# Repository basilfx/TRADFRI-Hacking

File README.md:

# Hacking IKEA TRÅDFRI

  * [Introduction](#introduction)
  * [TRÅDFRI modules](#trådfri-modules)
  * [Product teardowns](#product-teardowns)
  * [Firmware hacking](#firmware-hacking)
  * [Other hacks](#other-hacks)
    * [EZSP Zigbee coordinator](#ezsp-zigbee-coordinator)
    * [Zigbee router](#zigbee-router)
    * [FLOALT brightness hack](#floalt-brightness-hack)
    * [Shortcut button "no double press" hack](#shortcut-button-no-double-press-hack)
    * [DOOM](#doom)
  * [Sources](#sources)
  * [License](#license)
  * [Safety](#safety)
  * [Disclaimer](#disclaimer)

## Introduction
The [IKEA TRÅDFRI](http://www.ikea.com/us/en/catalog/categories/departments/lighting/36812/)
family of products provide you with several home automation solutions that
interconnect using [Zigbee Light Link](http://www.zigbee.org/zigbee-for-developers/applicationstandards/zigbee-light-link/).
While the line-up initially only included lighting products, it includes power
switches and wireless window blinds as well.

Many of the TRÅDFRI are quite simple. For instance, if we take a simple light
bulb, it contains:

* Power supply
* LED driver
* IKEA TRÅDFRI module

The IKEA TRÅDFRI module is used in many of their products, and is actually
a small piece of circuit board with a few GPIO pins exposed. These pins are
then used to control the LED driver.

The goal of this project is to provide information about the IKEA TRÅDFRI
modules and products, so you can start hacking them. For example:

* Take apart a light bulb, and use the module board, to control your own
  lighting solutions.
* Create custom boards for wall-mounted switches based on their dimmer buttons.
* Patch the firmware to dimming capabilies.
* Repurposing the modules by writing your own firmware.

To find relevant products, I have compiled a list of IKEA TRÅDFRI products in
[PRODUCTS.md](PRODUCTS.md). A teardown of has also been provided for some
products.

## TRÅDFRI modules
So far, a few variations of the TRÅDFRI modules have been identified. They are
all using microcontrollers manufactured by Silicon Labs. The modules that have
been identified are:

* ICC-1
* ICC-A-1
* MGM210L

Some other products, such as the line-up of remote controls, have a dedicated
circuit board that integrate a microcontroller directly (i.e. no separate
module board).

More details and pictures on these modules can be found in
[MODULES.md](MODULES.md).

## Product teardowns
Be sure to check out the [PRODUCTS.md](PRODUCTS.md) on more details on products
that have been reversed-engineered. There are product teardown photos,
schematics, firmware dumps, firmware analysis and more.

If you have any products not in the list, please contribute! If you have any
teardown photos, firmware files or other information, I'd like to add it to the
list.

## Firmware hacking
The TRÅDFRI products use an ARM Cortex M-series microcontroller. There are
plenty of tools for these types of microcontrollers to get started on reversing
firmware files and write your own firmwares.

* Find dumps of firmware files in the OTA [folder](contrib/firmwares/ikea-ota).
* Checkout the [RIOT-OS](contrib/firmwares/riot-os) folder for more information
  on custom firmware development. You can use this as a starting point.
* Reference information on dumping firmware images [here](docs/firmware_dumping/README.md).
* Learn how to inspect the firmware for reverse-enginering in [this](docs/firmware_reversing)
  folder.
* Build a [development board](contrib/pcbs/devboard) for easy access to a
  TRÅDFRI module's pins.

## Other hacks
Some people have came up with alternative uses for the TRÅDFRI modules. Here
are a few:

### EZSP Zigbee coordinator
It is possible to load the Silicon Labs EmberZNet Zigbee coordinator firmware
on an ICC-1 or ICC-A-1. This allows you to use the module to set-up your own
Zigbee network.

MattWestb has provided a guide and firmware [here](https://github.com/MattWestb/IKEA-TRADFRI-ICC-A-1-Module).

### Zigbee router
Several users have [modified](https://community.home-assistant.io/t/sonoff-zbbridge-sonoff-zigbee-bridge-from-itead/187346/88)
the TRÅDFRI routers to improve the performance, by adding an external antenna.

This applies to the ICC-A-1 modules only, but it should be very interesting
if a the TRÅDFRI routers will use the newer MGM210L modules, because they offer
a solder pad for an external antenna.

### FLOALT brightness hack
[zw](https://github.com/zw) has patched the firmware of his FLOALT LED panel to
have an improved range of brightness levels. A guide to perform the firmware
patch has been contributed [here](https://github.com/zw/TRADFRI-Hacking/tree/master/hacks/L1527).

### Shortcut button "no double press" hack
Simon has [patched](https://github.com/nomis/ikea-tradfri-e1812) the firmware
of the E1812 shortcut button to disable the double press feature, getting rid
of the 400ms delay on single presses.

### DOOM
A version of DOOM was port to the IKEA TRÅDFRI MGM210L modules, including a
custom contrller. The project is documented [here](https://next-hack.com/index.php/2021/06/12/lets-port-doom-to-an-ikea-tradfri-lamp/)
and the source code can be found [here](https://github.com/next-hack/MG21DOOM).

## Sources
I have gathered some information from the following sources:

* [IKEA TRÅDFRI hacking](https://tradfri.blogspot.nl)
* [TRÅDFRI: ESP8266-Lampen-Gateway](https://www.heise.de/make/artikel/Ikea-Tradfri-Anleitung-fuer-ein-ESP8266-Lampen-Gateway-3598411.html)
* [TRÅDFRI Zigbee Light Link module](https://diystuff.nl/tradfri/tradfri-zigbee-light-link-module)
* [TRÅDFRI Wall switch](https://wiki.permejdal.dk/TR%C3%85DFRI_wall_switch)

## License
See the [LICENSE.md](LICENSE.md) file (CC-BY-4.0).

## Safety
Some TRÅDFRI products are mains powered. If you don't know what that means, then
stop right now. Please read [this](docs/working_safely) for more information on
working safely on mains-connected devices.

## Disclaimer
This page and its content is not affiliated with IKEA of Sweden AB.

The purpose of this project is to learn and improve using reverse engineering
techniques. Use this information on your own risk. You will void your warranty.

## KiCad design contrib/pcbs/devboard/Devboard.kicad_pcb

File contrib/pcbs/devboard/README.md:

# Devboard
Development board to house an ICC-A or ICC-A-1 TRÅDFRI module.

## Known issues
* This board has a non-optimal design for wireless usage. However, the main
  goal of this board is to provide easier pin access.

## Pictures

## Board

## Schema
You can find the schema [here](Devboard.pdf).

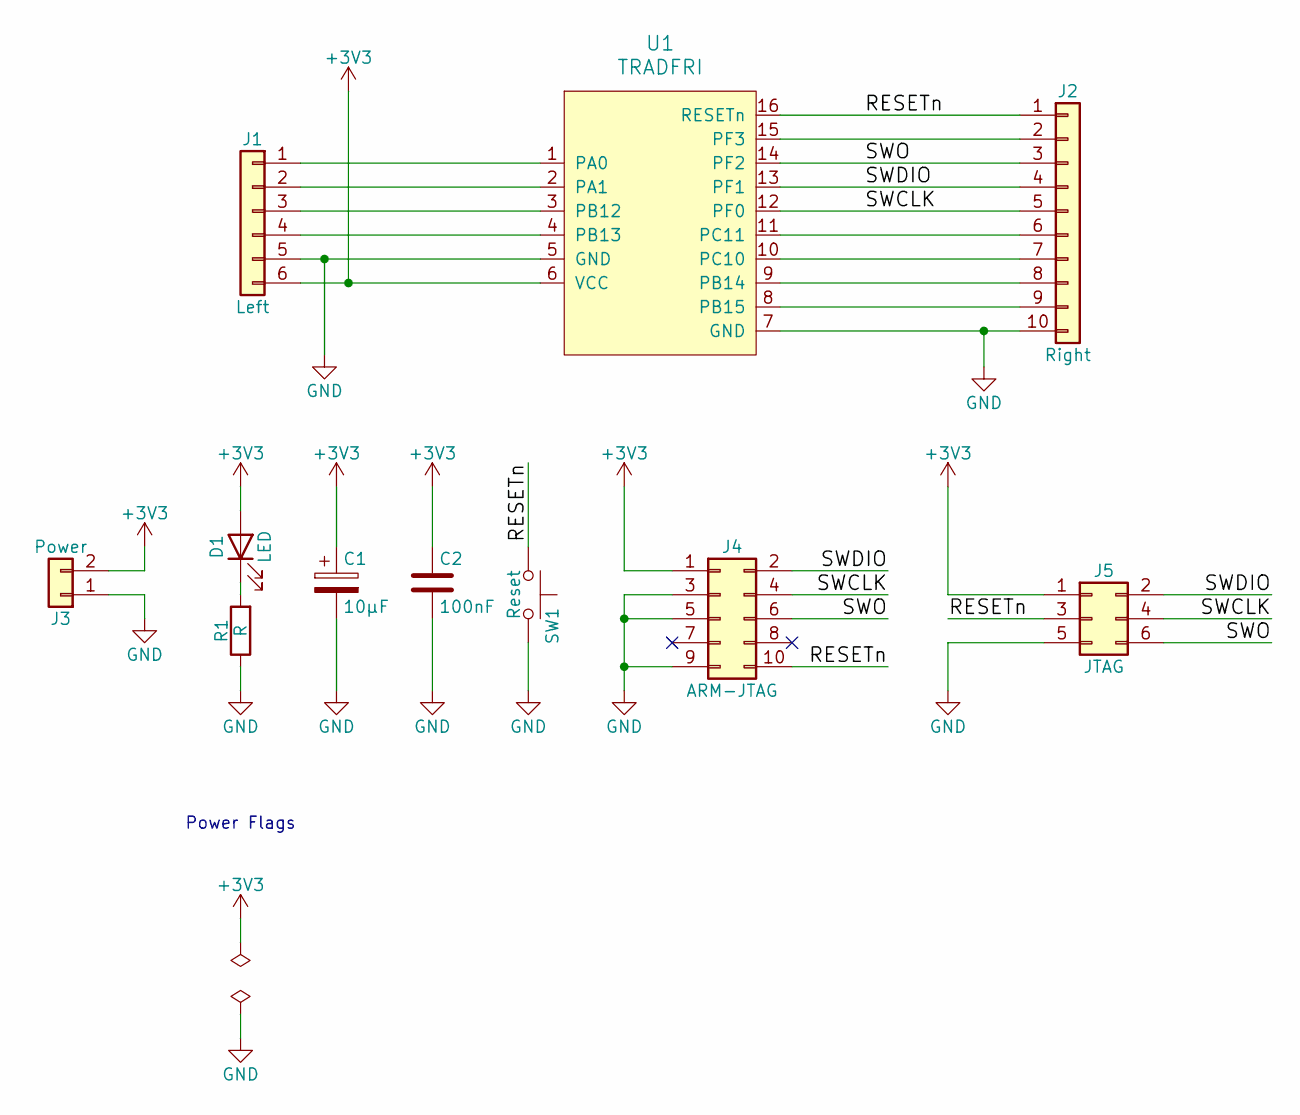
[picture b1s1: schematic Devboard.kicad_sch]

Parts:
C1: 10µF; CP_Elec_3x5.3
C2: 100nF; C_0805_2012Metric_Pad1.18x1.45mm_HandSolder
D1: LED; LED_0805_2012Metric_Pad1.15x1.40mm_HandSolder
J1: Left; PinHeader_1x06_P2.54mm_Vertical
J2: Right; PinHeader_1x10_P2.54mm_Vertical
J3: Power; PinHeader_1x02_P2.54mm_Vertical
J4: ARM-JTAG; PinHeader_2x05_P1.27mm_Vertical
J5: JTAG; PinHeader_2x03_P2.54mm_Vertical
R1: R; R_0805_2012Metric_Pad1.20x1.40mm_HandSolder
SW1: Reset; SW_PUSH_6mm
U1: TRADFRI; TRADFRI_PCB2.0

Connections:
+3V3: C1.1, C2.1, D1.2 (A), J1.6, J3.2, J4.1, J5.1, U1.6 (VCC)
/RESETn: J2.1, J4.10, J5.3, SW1.1, U1.16 (RESETn)
/SWCLK: J2.5, J4.4, J5.4, U1.12 (PF0)
/SWDIO: J2.4, J4.2, J5.2, U1.13 (PF1)
/SWO: J2.3, J4.6, J5.6, U1.14 (PF2)
GND: C1.2, C2.2, J1.5, J2.10, J3.1, J4.3, J4.5, J4.9, J5.5, R1.1, SW1.2, U1.5 (GND), U1.7 (GND)
unnamed: D1.1 (K), R1.2
unnamed: J1.1, U1.1 (PA0)
unnamed: J1.2, U1.2 (PA1)
unnamed: J1.3, U1.3 (PB12)
unnamed: J1.4, U1.4 (PB13)
unnamed: J2.2, U1.15 (PF3)
unnamed: J2.6, U1.11 (PC11)
unnamed: J2.7, U1.10 (PC10)
unnamed: J2.8, U1.9 (PB14)
unnamed: J2.9, U1.8 (PB15)

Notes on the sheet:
Power Flags

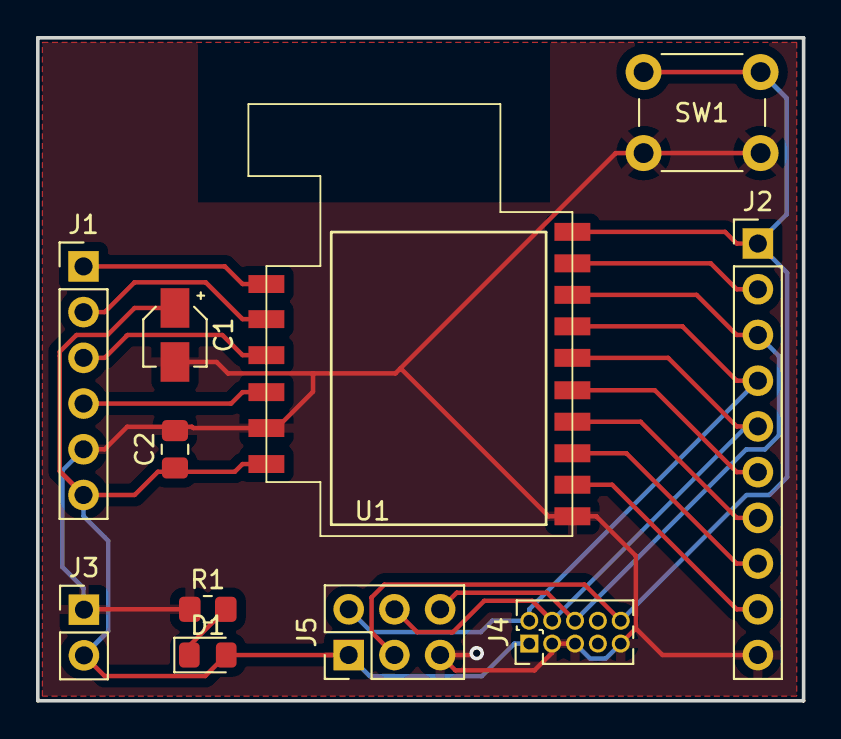
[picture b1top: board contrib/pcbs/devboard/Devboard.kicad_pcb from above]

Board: 2 copper layers, 42.5 x 36.8 mm, 11 parts (0 on the bottom side), 16 nets.

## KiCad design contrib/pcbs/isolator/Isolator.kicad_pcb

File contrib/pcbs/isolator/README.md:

# Isolator
Tiny board to isolate UART RX/TX from target board.

## Pictures

## Board

## Schema
You can find the schema [here](Isolator.pdf).

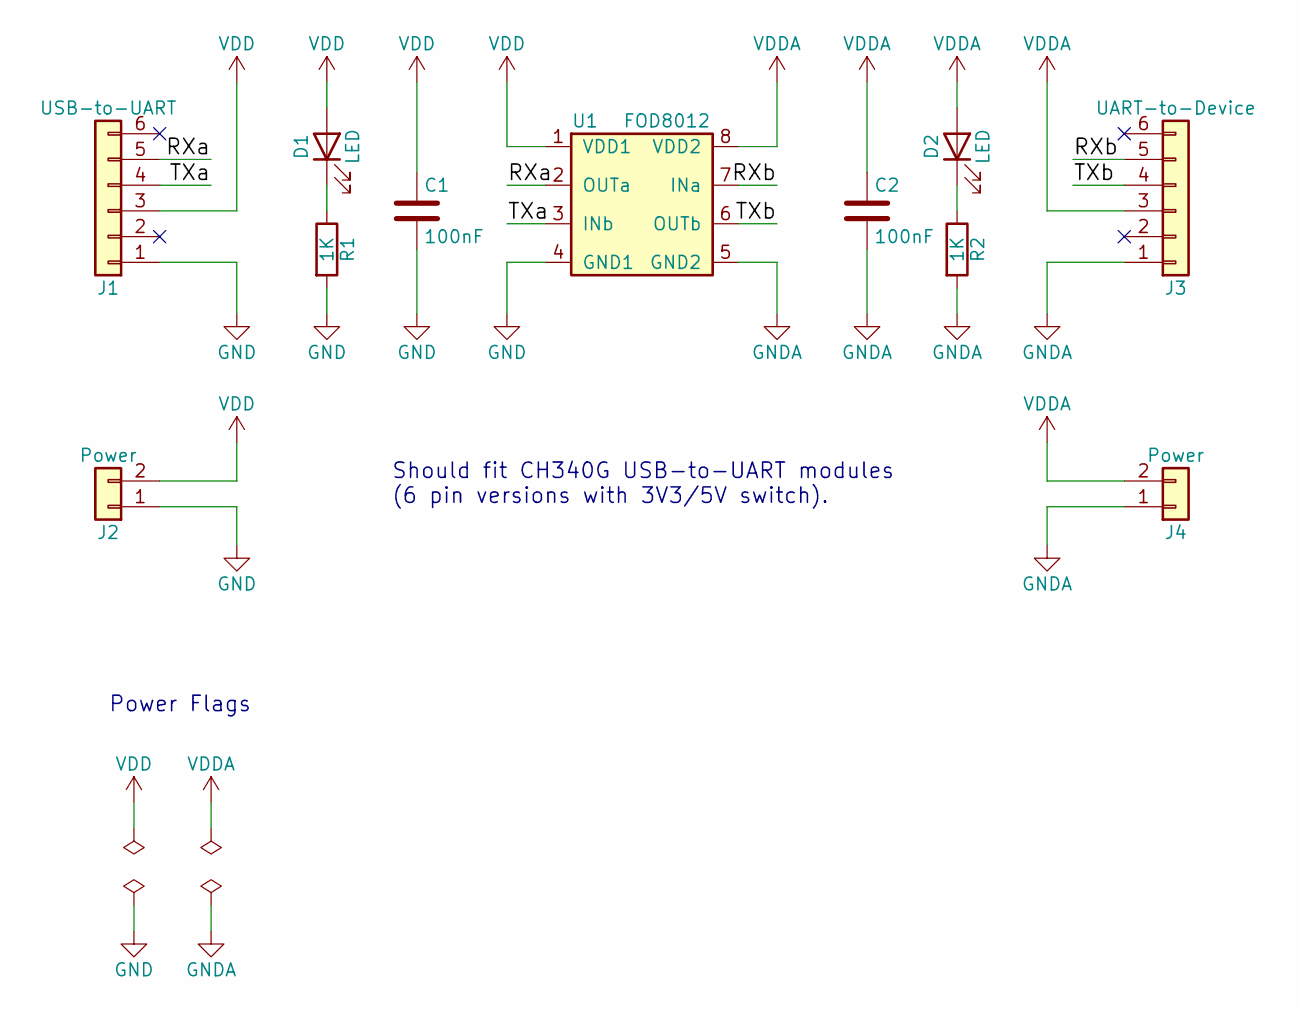
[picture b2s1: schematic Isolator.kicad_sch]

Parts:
C1, C2: 100nF; C_0805_2012Metric_Pad1.18x1.45mm_HandSolder
D1, D2: LED; LED_0805_2012Metric_Pad1.15x1.40mm_HandSolder
J1: USB-to-UART; PinHeader_1x06_P2.54mm_Vertical
J2, J4: Power; PinHeader_1x02_P2.54mm_Vertical
J3: UART-to-Device; PinHeader_1x06_P2.54mm_Vertical
R1, R2: 1K; R_0805_2012Metric_Pad1.20x1.40mm_HandSolder
U1: FOD8012; SOIC-8-N

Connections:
/RXa: J1.5, U1.2 (OUTa)
/RXb: J3.5, U1.7 (INa)
/TXa: J1.4, U1.3 (INb)
/TXb: J3.4, U1.6 (OUTb)
GND: C1.2, J1.1, J2.1, R1.2, U1.4 (GND1)
GNDA: C2.2, J3.1, J4.1, R2.2, U1.5 (GND2)
unnamed: D1.1 (K), R1.1
unnamed: D2.1 (K), R2.1
VDD: C1.1, D1.2 (A), J1.3, J2.2, U1.1 (VDD1)
VDDA: C2.1, D2.2 (A), J3.3, J4.2, U1.8 (VDD2)

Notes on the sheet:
Power Flags
Should fit CH340G USB-to-UART modules (6 pin versions with 3V3/5V switch).

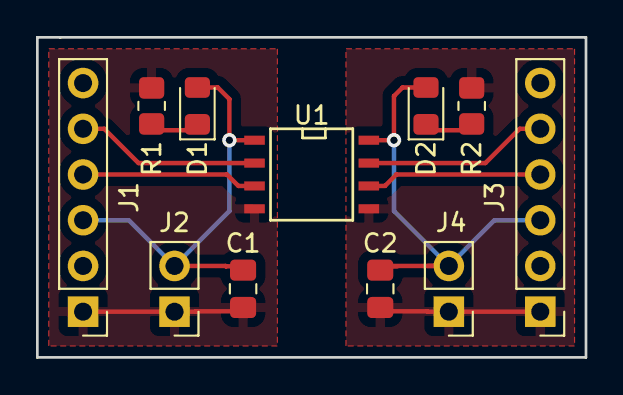
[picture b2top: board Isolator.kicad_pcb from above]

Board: 2 copper layers, 30.5 x 17.8 mm, 11 parts (0 on the bottom side), 10 nets.

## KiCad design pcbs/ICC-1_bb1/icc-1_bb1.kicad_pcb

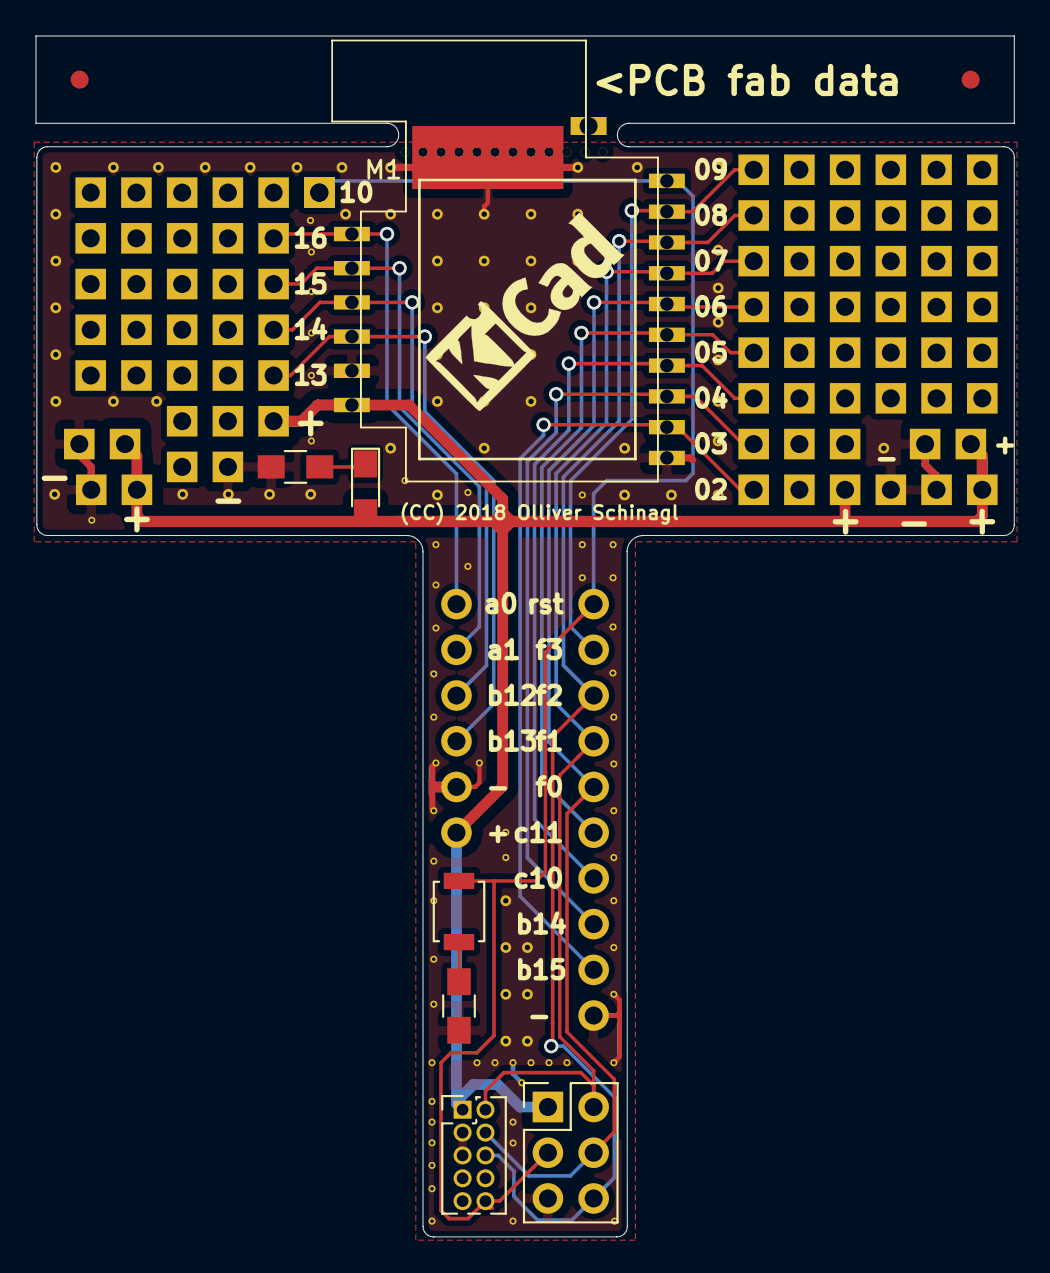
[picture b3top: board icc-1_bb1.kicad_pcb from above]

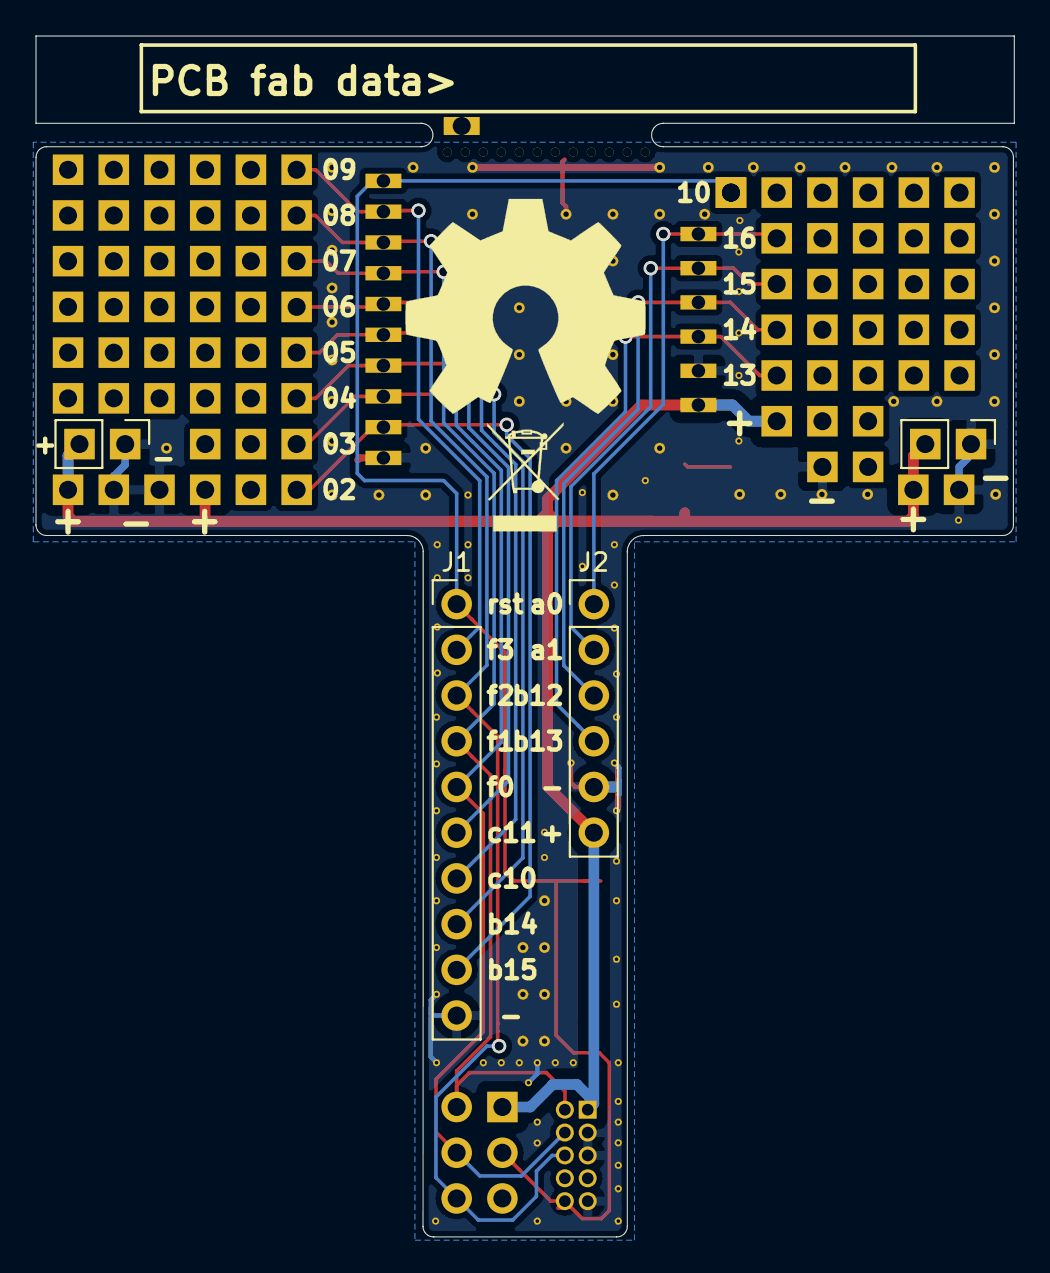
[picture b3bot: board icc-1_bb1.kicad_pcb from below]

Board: 2 copper layers, 54.3 x 66.7 mm, 13 parts (4 on the bottom side), 17 nets.

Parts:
D1: POWER_LED; LED_0805_HandSoldering
FID1, FID2: fiducial
J1: Right; Pin_Header_Straight_1x10_Pitch2.54mm
J2: Left; Pin_Header_Straight_1x06_Pitch2.54mm
J3: JTAG; Pin_Header_Straight_2x03_Pitch2.54mm
J4: ARM-JTAG; Pin_Header_Straight_2x05_Pitch1.27mm
J5, J6: Power; Pin_Header_Straight_1x02_Pitch2.54mm
M1: ICC-1; ICC-1_POLY_PCB2.0_through-hole
R1: R; R_0805_HandSoldering
R2: 100R; R_0805_HandSoldering
SW1: RESET; SW_SPST_B3U-1000P

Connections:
+3V3: D1.2, J2.6, J3.1, J4.1, J5.2, J6.2, M1.11
/RESETn: J1.1, J3.3, J4.10, M1.10, SW1.2
/SWCLK: J1.5, J3.4, J4.4, M1.6
/SWDIO: J1.4, J3.2, J4.2, M1.7
/SWO: J1.3, J3.6, J4.6, M1.8
GND: J1.10, J2.5, J3.5, J4.3, J4.5, J4.9, J5.1, J6.1, M1.1, M1.12, R1.1, R2.2
unnamed: D1.1, R1.2
unnamed: J1.2, M1.9
unnamed: J1.6, M1.5
unnamed: J1.7, M1.4
unnamed: J1.8, M1.3
unnamed: J1.9, M1.2
unnamed: J2.1, M1.16
unnamed: J2.2, M1.15
unnamed: J2.3, M1.14
unnamed: J2.4, M1.13
unnamed: R2.1, SW1.1

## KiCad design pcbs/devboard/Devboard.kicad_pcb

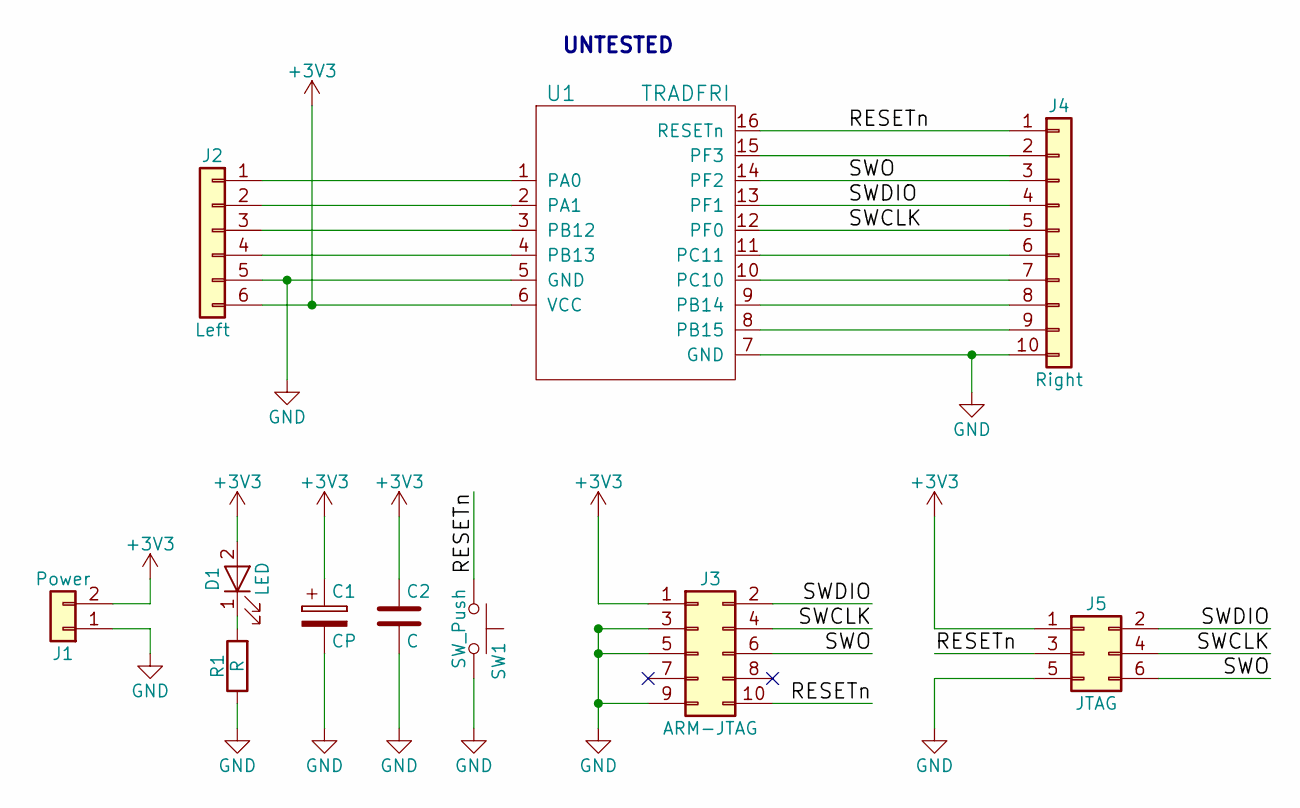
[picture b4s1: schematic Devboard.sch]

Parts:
C1: CP; CP_Elec_3x5.3
C2: C; C_0805_HandSoldering
D1: LED; LED_0805_HandSoldering
J1: Power; Pin_Header_Straight_1x02_Pitch2.54mm
J2: Left; Pin_Header_Straight_1x06_Pitch2.54mm
J3: ARM-JTAG; Pin_Header_Straight_2x05_Pitch1.27mm
J4: Right; Pin_Header_Straight_1x10_Pitch2.54mm
J5: JTAG; Pin_Header_Straight_2x03_Pitch2.54mm
R1: R; R_0805_HandSoldering
SW1: SW_Push; SW_PUSH_6mm
U1: TRADFRI; TRADFRI_PCB2.0

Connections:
+3V3: C1.1, C2.1, D1.2 (A), J1.2, J2.6, J3.1, J5.1, U1.6 (VCC)
/RESETn: J3.10, J4.1, J5.3, SW1.1, U1.16 (RESETn)
/SWCLK: J3.4, J4.5, J5.4, U1.12 (PF0)
/SWDIO: J3.2, J4.4, J5.2, U1.13 (PF1)
/SWO: J3.6, J4.3, J5.6, U1.14 (PF2)
GND: C1.2, C2.2, J1.1, J2.5, J3.3, J3.5, J3.9, J4.10, J5.5, R1.1, SW1.2, U1.5 (GND), U1.7 (GND)
unnamed: D1.1 (K), R1.2
unnamed: J2.1, U1.1 (PA0)
unnamed: J2.2, U1.2 (PA1)
unnamed: J2.3, U1.3 (PB12)
unnamed: J2.4, U1.4 (PB13)
unnamed: J4.2, U1.15 (PF3)
unnamed: J4.6, U1.11 (PC11)
unnamed: J4.7, U1.10 (PC10)
unnamed: J4.8, U1.9 (PB14)
unnamed: J4.9, U1.8 (PB15)

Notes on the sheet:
UNTESTED

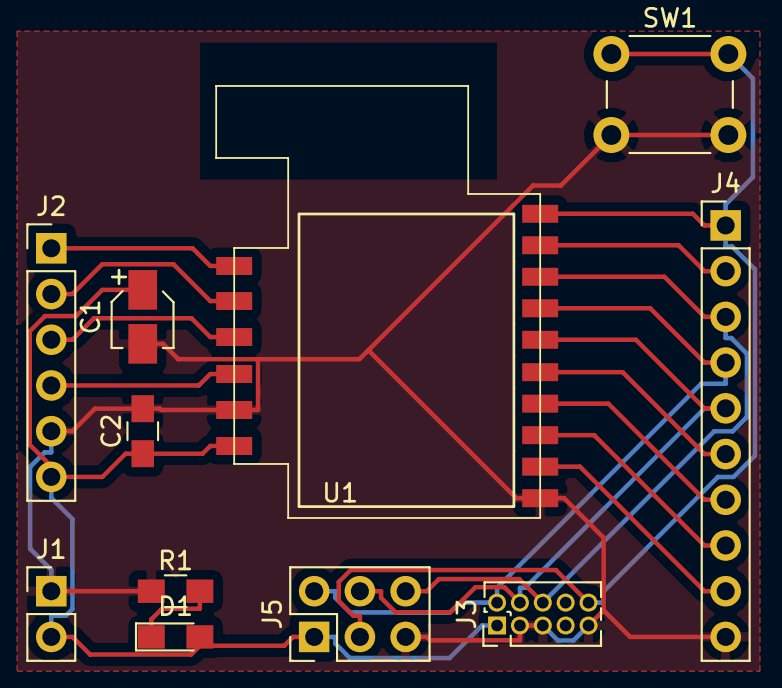
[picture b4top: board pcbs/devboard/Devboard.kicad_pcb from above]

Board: 2 copper layers, 11 parts (0 on the bottom side), 16 nets.

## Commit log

2017-11-15 Add gitignore.
2017-11-15 Add initial version of README.md
2017-11-15 Add note on custom firmware.
2017-11-16 Ignore Kicad files.
2017-11-16 Add schematic + pcb for an UART isolator (untested).
2017-11-16 Add schematic + pcb for a development board (untested).
2017-11-17 Clearify load/dump commands.
2017-11-17 Add parts section.
2017-11-17 Add original firmware of GU-10 LED light.
2017-11-17 Add two test applications.
2017-11-17 Add more photos.
2017-11-17 Update README with links to firmware.
2017-11-18 Updated devboard pcb, accidentally swapped GND and VCC line.
2017-11-18 Add list of IKEA TRADFRI products.
2017-11-19 Add CAD files of PCB.
2017-11-19 Updated PCBs
2017-11-19 Add 3D PCB renders.
2017-11-19 Add teardown pictures in separate folder.
2017-11-19 Identified SPI flash.
2017-11-19 Dump strings and heatmap of original firmware.
2017-11-19 Rename models to products.
2017-11-19 I'm more certain about the SPI flash chip used.
2017-11-19 Add analysis of firmware.
2017-11-19 Add disclaimer.
2017-11-19 Link to firmware analysis.
2017-12-27 Isolator devboard built and tested.
2018-03-05 Add link to more information about the module.
2018-03-05 Added information on the universal dimmer.
2018-03-05 Added information about 1537R6.
2018-05-21 Fixed edge cuts. Upgrade tot Kicad 5.0-rc2.
2018-05-21 Update PDF schematic and PNG image.
2018-05-29 Create LED Power Supply
2018-05-30 Add OTA firmwares
    Dresden-Electronik has a nice python script that allows one to download
    the Over The Air Update files from the ikea servers [0]. For archiving purposes
    it is usefull to mirror them here.
    Also attached a few versions of version_info.json pointing to these public files.
    [0] https://github.com/dresden-elektronik/deconz-rest-plugin/blob/master/ikea-ota-download.py
2018-06-03 Name appropiate device
    The pictured devices in the source under ICPSHC24 is actually a FLOALT L1529. This can be seen on the background where it says L1529. The transformer is part of the FLOALT in this case. This also is 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
2018-06-03 Add ICPSHC24-10EU-IL-1 (10W LED driver/dimmer)
    After getting a 10 Watt transformer I opened it for documentation purposes.
    Find the teardown and product information.
    The power control unit appears to be identical to the ICPSHC24-30EU-IL-1
    as can be seen in PR #7. Further investigation is needed and likely
    deblobbing/soldering to confirm some traces.
    U1 does not seem to be controlled by the rf-module, but is very likely to be a buck converter (24 V -> 3.3 V).
2018-06-20 Pinout / wiring of the motion sensor board
    Obtained by groping the PCB with a continuity tester, and carried over
    from personal notes.
2018-06-20 Add files via upload
    Images of LED1537R6, as expected two rings of led, and 3 connections to ledprint, the print is kind casted into the fitting, so only three pins to play with, will measure them
2018-06-21 Pictures of LED1537R6 with potting removed
2018-06-21 Connect LEDBERG
2018-06-21 connected
2018-08-23 Update README.md
    256 KiB is 0x40000 instead of 0x4000. Fixes #19.
2018-08-27 products: Fix-up PF symbols
    The PF symbols have been incorrectly commited. This patch fixes that.
2018-08-27 schematic: ICPSLC24-10NA PWM module
    With the teardown of the ICPSLC24-10NA module complete, a KiCAD
    schematic has been drawn to understand its exact function.
    A PCB design has been excluded at this moment.
    Note: The buck regulator is not part of the standard library, but
    is on its way upstream to the digi-key kicad repo and likely the
    default kicad repo as well.
2018-08-27 products: Have the ICPSLC24-10NA be as an 'include'
    The ICPSLC24-10NA is on both the ICPSHC24-30EU-IL-1 and ICPSHC24-10EU-IL-1.
    To reduce duplication split it off in its own section.
2018-08-27 teardown: ICSPSLC24-10NA controller
    The ICSPSLC24-10NA controller sits at the end of the LED driver chain
    on the LED drivers such as the ICPSHC24-30EU-IL-1 and ICSPHC24-10EU-IL-1.
    It takes 24 Volts as its input and toggles its single output (On/Off/PWM).
2018-08-28 teardown: Add ICPSHC24-30EU-IL-1 (30W LED driver/dimmer)
    The ICPSHC24-30EU-IL-1 seems to be the big brother of
    the ICPSHC24-10EU-IL-1 with the only real difference being the power
    supply.
    This patch takes ludwo88's PR #7 photo's and creates a more appropiate
    merge request.
    Closes #7
2018-08-28 Add a breadboard friendly ICC-1 Carrier board
    This patch adds a(nother) devboard suitable of sticking onto a
    breadboard. It uses some spare room for prototyping.
2018-08-28 (Re-)create parts based on datasheets
    This commit creates the ICC-1 poly modules based on their limited
    datasheet [0] information. The datasheet properly lists pin numbers
    and acurate dimensions, such as the most important dimension,
    pin locations.
    The parts are added as two variants, one a pure SMD mount and one where the
    SMD pats have received throug-hole mounts. This allows for via-less routing
2018-09-18 Added guide to disassemble firmware dump in IDA
2018-09-30 Add dimmer pinout + schematic
2018-10-18 firmwares: Add cron script to have archive.org index the json
    This is mostly for archival purposes as I am running the once a week
    via cron.weekly.
2020-01-11 Added images of the Trådfri modules I found in a January 2020 bulb.
2020-01-11 Updated the images of the November 2017 Trådfri modules.
2020-01-11 Add teardown of the LED1837R5.
2020-01-11 Minor update to PRODUCTS.md
2020-01-11 Add pictures of the newer ICC-1-A module.
2020-01-11 Minor update to README.md
2020-01-11 Add new pinouts of both ICC-1 and ICC-1-A modules.
2020-01-11 Add picture of soldered development board.
2020-01-11 Add teardown of LED1537R6.
    Pictures and information by @rezolf, contributed via
    https://github.com/basilfx/TRADFRI-Hacking/pull/17.
2020-01-11 Add an additional source of information.
2020-01-11 Upload new versions of the firmware, add links to sources.
2020-01-11 Missing address in loadbin command.
2020-01-11 Add dumps of the LED1837R5 v2.1.022 firmware.
2020-01-11 Add information on SPI NOR Flash contents.
2020-01-12 Correct ICC-1-A into ICC-A-1.
2020-01-16 Added E1745 Motion Sensor
    Added the E1745 Motion Sensor, an updated (and kind of worse) version of the E1525. Seems to be pretty similar tho with some differences on the PCB markings. Further investigation and firmware dumpin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
2020-01-16 Fixed "#flashing-using-jtag" not clickable
    Still had an old #flashing instead of #flashing-using-jtag
2020-02-29 Replace dead link
2020-08-15 Add E1525 Details
    Added a schematic and additonal information on the E1525 sensor.
2020-08-15 Add pictures
    Added front and back photographs of the PCB
2021-01-11 Extend disclaimer.
2021-01-11 Add LED1923R5
    Mentioned in https://github.com/basilfx/TRADFRI-Hacking/issues/39.
2021-01-11 Enforcing line length for Git.
    Longer lines are harder to diff when hard-wrapping.
2021-01-11 Fixed formatting and added pictures of E1745.
2021-01-11 Add photos of module PCB
2021-01-11 Add MGM210L modules.
    Also restructure the information to better suite the new module.
2021-01-11 Rename images of the modules.
    Prepares for new module.
2021-01-11 Structure images and schematics.
2021-01-11 Add ToC.
2021-01-11 Document other memory addresses.
2021-01-11 Document EZSP firmware.
2021-01-11 Add link to COAP protocol used by the gateway.
2021-01-11 Restructure develoment section.
2021-01-12 Added Product groups and IKEA names to list
2021-01-12 Fix picture links
2021-01-12 Fix ToC
2021-01-12 Add ZigBee router hack.
2021-01-12 Add FLOALT brightness hack.
2021-01-12 Document external antenna.
2021-01-14 update product IDs into list of Products
2021-01-14 Update Product Overview
2021-01-17 Added SILVERGLANS LED driver
2021-01-21 added JORMLIEN and SURTE to list of products
2021-02-12 Added shortcut button
2021-06-14 Add DOOM port as another hack
2023-07-19 Add teardown of E2201 - RODRET
    https://fcc.report/FCC-ID/FHO-E2201
2023-09-24 Add E1812 shortcut button
2024-03-15 Add teardown of E2123 - Symfonisk Sound Remote Gen2
    Module used: https://www.silabs.com/wireless/zigbee/efr32mg21-series-2-modules/device.mgm210la22jnf
2024-06-01 Add IKEA PARASOLL door/window sensor
2024-08-20 Add hardware info about BADRING water leakage sensor (E2202)
2024-11-18 Add two scope screenshots
    These screenshots show how the PARASOLL reads the switch status about
    five times per second, for approximately 30 milliseconds.
2024-11-18 Move modules to separate directory
2024-11-18 Rename teardowns to products
2024-11-18 Move less-related stuff to contrib folder
2024-11-18 Fix image links
2024-11-18 Move firmwares to appropriate product folder
2024-11-18 Move RIOT-OS firmware examples to contrib
    This is how it all started, but it is not the 'core' anymore. Still
    relevant to keep though.
2024-11-18 Move archived OTA files to contributed
    I currently have no better place to store them, because from the file
    names it is not clear to which product they belong.
    Might revisit this in the future.
2024-11-18 Move firmware reversing to documentation folder
2024-11-18 Add .editorconfig file
2024-11-18 Add explicit license file
    This project already used the CC-BY-4.0 license, but it was never very
    explicit. Add LICENSE.md and refer to this file for more information.
2024-11-21 Move the 'working safely' section
    Move this to the documentation folder. This only moves the content,
    but it does not update the references.
2024-11-23 Rework contributed PCBs
    * Upgrade to KiCad 8
    * Improved PCBs
    * Added Makefile for automation of schema and board renders
2024-11-23 Update README.md
    URL changed iptables.dk > permejdal.dk
2024-11-23 Add explanation of RIOT-OS firmware files
2024-11-23 Add README for OTA dumps
2024-11-23 Move the firmware dumping to documentation
2024-11-23 Add types of modules to modules section
2024-11-24 Rework the main README to be more concise
2024-11-24 Move all products to separate README
    Also re-organize the PRODUCTS.md file
2024-11-25 Add product names next to product codes
    This will help finding products based on their marketed name.
2024-11-25 Add IKEA ÅSKVÄDER on/off button
2024-11-25 Add IKEA ORMANÄS led strip
2024-11-25 Add IKEA TRETAKT smart switch
2024-11-28 Add IKEA INSPELNING smart switch
